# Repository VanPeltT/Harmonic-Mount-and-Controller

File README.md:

# Harmonic Drive Telescope Mounts
# A DIY Approach to Precision Astronomical Viewing and Astrophotography
 
 This project, developed by Thomas Van Pelt and Greg Booher, consists of two
 harmonic drive telescope mounts designed for precise astronomical observations. 
 The project showcases both a robust, aluminum-based mount and a more 
 lightweight, entirely 3D-printed variant.

# Overview

  Target Audience: This document is intended for hobbyists, makers, and astronomers 
  interested in building their own high-performance telescope mounts.

# Project Goals:

  Develop affordable, customizable telescope mounts using harmonic drive technology.
  Offer a lightweight and portable 3D-printed option.
  Provide detailed documentation and open-source designs for community use.
  Achieve precise pointing and tracking for astrophotography applications.

# Unique Selling Points:

  Cost-effective: Harmonic drive technology offers high precision at a reasonable 
      cost compared to traditional gear drives.
  Customizable: Modular design allows for adaptations based on telescope weight 
      and user needs.
  Open-source: Hardware and software designs are freely available for modification 
      and improvement.

# Mounts Description

# Mount 1: Aluminum Anodized Mount

  Material: Aluminum (anodized by Greg Booher)
  Motors: 2 NEMA 17 motors with a 27:1 gearbox
  Harmonic Drive: CSF-17-100-2UH-LW with a 100:1 reduction
  Controllers: TMC2209 stepper controllers
  Microcontroller: Teensy 4.0 running OnStep
  Connectivity: Bluetooth and WiFi
  Design Contributions:
    Greg Booher: Machining and Anodizing the aluminum parts
    Thomas Van Pelt: Designing and creating the covers and printed circuit boards

# Mount 2: 3D Printed Mount

  Material: CF-PETG (Carbon Fiber Polyethylene Terephthalate Glycol)
  Motors: 2 NEMA 17 motors with a 30:1 harmonic drive
  Controllers: Same PCB control board as the larger mount
  Connectivity: Bluetooth and WiFi
  Design Contributions: Entirely designed and 3D printed

# Development Timeline

  The project has been under development for over six months and was demonstrated 
  to the Escambia Amateur Astronomy Association in July 2024.

# Future Work
  Thomas Van Pelt plans to further develop the larger mount, integrating it with a 
  custom PCB and software specifically designed for the Raspberry Pi, enhancing the 
  mount's control capabilities and user interface.

# Getting Started

# Prerequisites:

  Teensy 4.0
  TMC2209 stepper controllers
  NEMA 17 motors
  CSF-17-100-2UH-LW harmonic drive for the aluminum mount (or equivalent 100:1 harmonic drive)
  30:1 harmonic drive for the 3D printed mount
  OnStep firmware
  Bluetooth and WiFi modules
  
# Assembly Instructions:

  1. Assemble the aluminum frame.
  2. Install the NEMA 17 motors and the 27:1 gearbox.
  3. Integrate the CSF-17-100-2UH-LW harmonic drive.
  4. Connect the TMC2209 stepper controllers to the Teensy 4.0.
  5. Connect the Bluetooth and WiFi modules to the Teensy 4.0.
  6. Upload OnStep firmware to the Teensy 4.0.
  7. Install the covers and PCBs designed by Thomas.

# Usage:

  1. Power on the system.
  2. Connect the mount to your computer or control device via Bluetooth or WiFi.
  3. Use OnStep software to control the telescope mount. (OnStep download and 
      configuration instructions can be found online)
  4. Adjust settings as necessary for precise astronomical tracking and observation.

# Contribution

  Contributions to further enhance the mounts are welcome. Please fork the 
  repository and submit pull requests.

# License

  This project is licensed under the MIT License.

  For more detailed information, please refer to the documentation in the repository or contact the developers:

  Thomas Van Pelt
  Greg Booher
  
  Happy Stargazing!

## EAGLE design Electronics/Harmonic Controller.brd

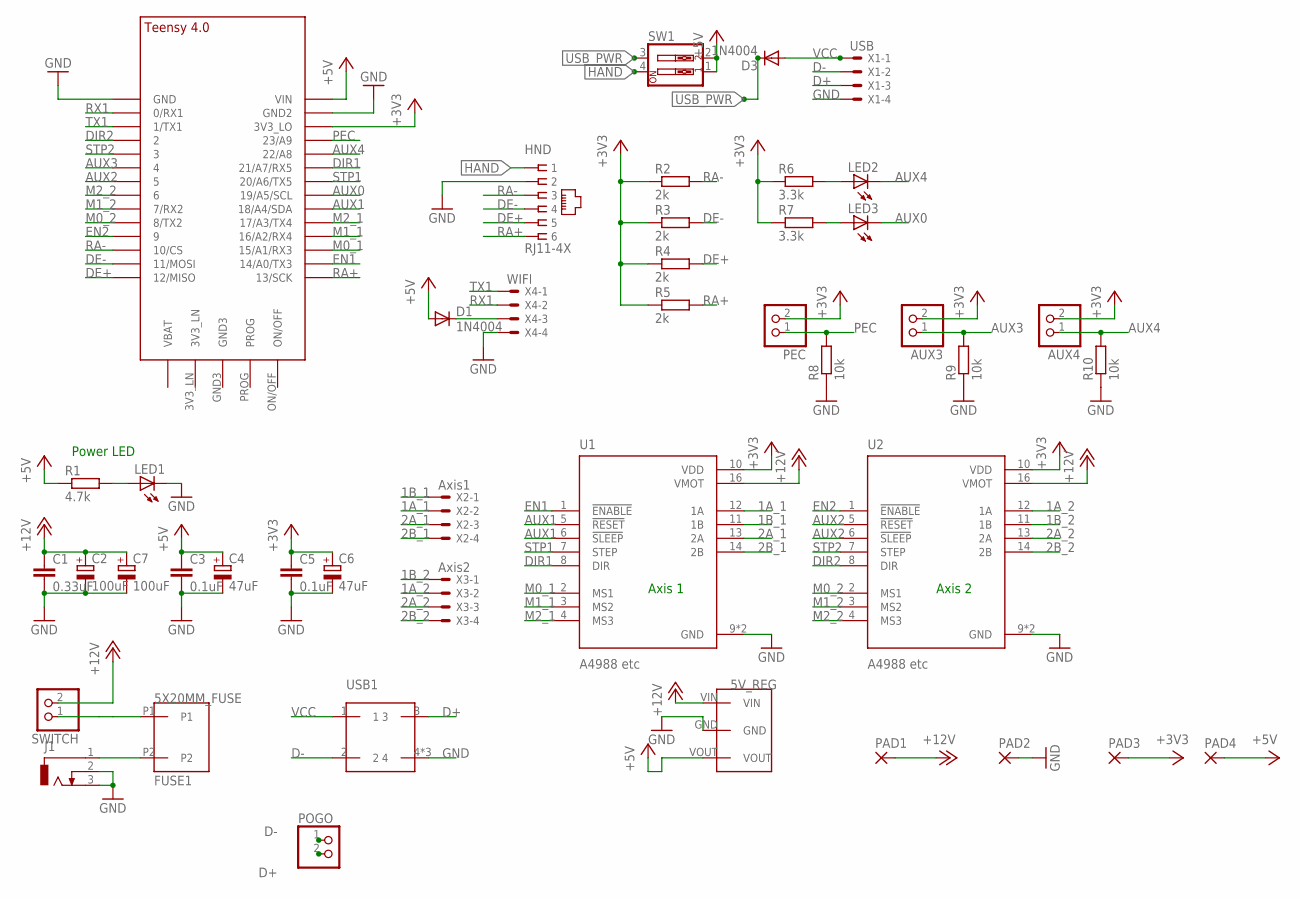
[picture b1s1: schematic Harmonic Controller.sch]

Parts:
5V_REG: TSR_5V
AUX3, AUX4: PINHD-1X2; 1X02
C1: 0.33uF; C050-024X044
C2, C7: 100uF; E5-8,5
C3, C5: 0.1uF; C050-024X044
C4, C6: 47uF; E5-8,5
D1, D3: 1N4004; DO41-10
FUSE1: 5X20MM_FUSE
HND: RJ11-4X; RJ11-NO_SHIELD
J1: DCJ0303
LED1, LED2, LED3: LED5MM
PAD1, PAD2, PAD3, PAD4: SMD2; SMD1,27-2,54
PEC: PINHD-1X2; 1X02
POGO: PINHD-1X2; 1X02
R1: 4.7k; 0207/7
R2, R3, R4, R5: 2k; 0207/7
R6, R7: 3.3k; 0207/7
R8, R9, R10: 10k; 0207/7
SW1: SW_DIP-2; EDG-02
SWITCH: PINHD-1X2; 1X02
U1, U2: A4988 etc; MODULE_A4988_STEPPER_MOTOR_DRIVER_CARRIER
U$1: TEENSY_4.0
USB1: USB-B_SOCKET
X1: USB; JST-XH-04-PACKAGE-ROUND-PAD
X2: Axis1; JST-XH-04-PACKAGE-LONG-PAD
X3: Axis2; JST-XH-04-PACKAGE-LONG-PAD
X4: WIFI; JST-XH-04-PACKAGE-LONG-PAD

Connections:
1A_1: U1.12 (1A), X2.2
1A_2: U2.12 (1A), X3.2
1B_1: U1.11 (1B), X2.1
1B_2: U2.11 (1B), X3.1
2A_1: U1.13 (2A), X2.3
2A_2: U2.13 (2A), X3.3
2B_1: U1.14 (2B), X2.4
2B_2: U2.14 (2B), X3.4
+3V3: AUX3.2, AUX4.2, C5.1, C6.+, PAD3.1, PEC.2, R2.1, R3.1, R4.1, R5.1, R6.1, R7.1, U1.10 (VDD), U2.10 (VDD), U$1.3V3_LO
+5V: 5V_REG.VOUT, C3.1, C4.+, D1.A, PAD4.1, R1.1, SW1.1, SW1.2, U$1.VIN
+12V: 5V_REG.VIN, C1.1, C2.+, C7.+, PAD1.1, SWITCH.2, U1.16 (VMOT), U2.16 (VMOT)
AUX0: LED3.K (C), U$1.19/A5/SCL
AUX1: U1.5 (!RESET), U1.6 (!SLEEP), U$1.18/A4/SDA
AUX2: U2.5 (!RESET), U2.6 (!SLEEP), U$1.5
AUX3: AUX3.1, R9.2, U$1.4/CANRX (4)
AUX4: AUX4.1, LED2.K (C), R10.2, U$1.22/A8
D+: POGO.2, USB1.3, X1.3
D-: POGO.1, USB1.2, X1.2
DE+: HND.5, R4.2, U$1.12/MISO
DE-: HND.4, R3.2, U$1.11/MOSI
DIR1: U1.8 (DIR), U$1.21/A7 (21/A7/RX5)
DIR2: U2.8 (DIR), U$1.2
EN1: U1.1 (!ENABLE), U$1.14/A0 (14/A0/TX3)
EN2: U2.1 (!ENABLE), U$1.9/CS (9)
GND: 5V_REG.GND, C1.2, C2.-, C3.2, C4.-, C5.2, C6.-, C7.-, HND.2, J1.2, J1.3, LED1.K (C), PAD2.1, R8.1, R9.1, R10.1, U1.9 (GND), U1.15 (GND), U2.9 (GND), U2.15 (GND), U$1.GND, U$1.GND2, USB1.4, USB1.P$1 (4), USB1.P$2 (4), X1.4, X4.4
HAND: HND.1, SW1.4
M0_1: U1.2 (MS1), U$1.15/A1 (15/A1/RX3)
M0_2: U2.2 (MS1), U$1.8 (8/TX2)
M1_1: U1.3 (MS2), U$1.16/A2 (16/A2/RX4)
M1_2: U2.3 (MS2), U$1.7 (7/RX2)
M2_1: U1.4 (MS3), U$1.17/A3 (17/A3/TX4)
M2_2: U2.4 (MS3), U$1.6
unnamed: FUSE1.P2, J1.1
unnamed: FUSE1.P1, SWITCH.1
unnamed: LED1.A, R1.2
unnamed: D1.C, X4.3
unnamed: LED2.A, R6.2
unnamed: LED3.A, R7.2
PEC: PEC.1, R8.2, U$1.23/A9
RA+: HND.6, R5.2, U$1.13/SCK
RA-: HND.3, R2.2, U$1.10/CS
RX1: U$1.0/RX (0/RX1), X4.2
STP1: U1.7 (STEP), U$1.20/A6 (20/A6/TX5)
STP2: U2.7 (STEP), U$1.3/CANTX (3)
TX1: U$1.1/TX (1/TX1), X4.1
USB_PWR: D3.C, SW1.3
VCC: D3.A, USB1.1, X1.1

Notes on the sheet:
Power LED
Axis 1
Axis 2

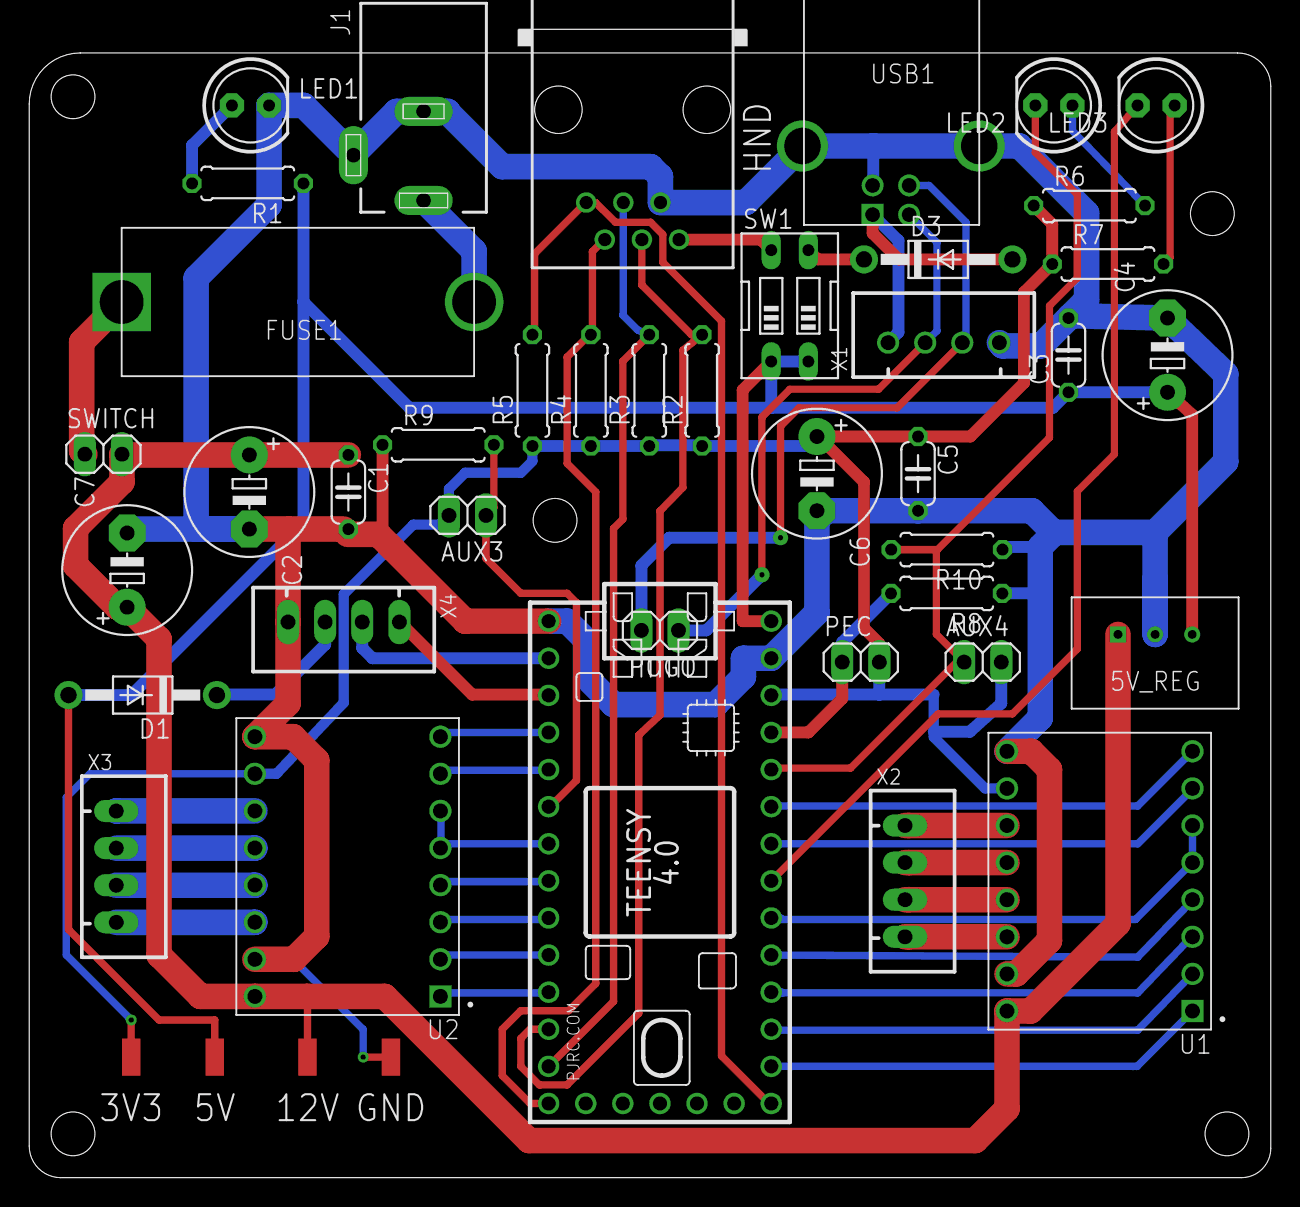
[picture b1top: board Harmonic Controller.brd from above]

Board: 2 copper layers, 85.0 x 78.6 mm, 44 parts (0 on the bottom side), 47 nets.

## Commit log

2024-07-26 Add files via upload
    Electronics
2024-07-26 Add files via upload
    Bonus and Future Work
2024-07-26 Add files via upload
    Gerbers and config files for OnStep
2024-07-26 Add files via upload
    Mini Mount Gerbers
